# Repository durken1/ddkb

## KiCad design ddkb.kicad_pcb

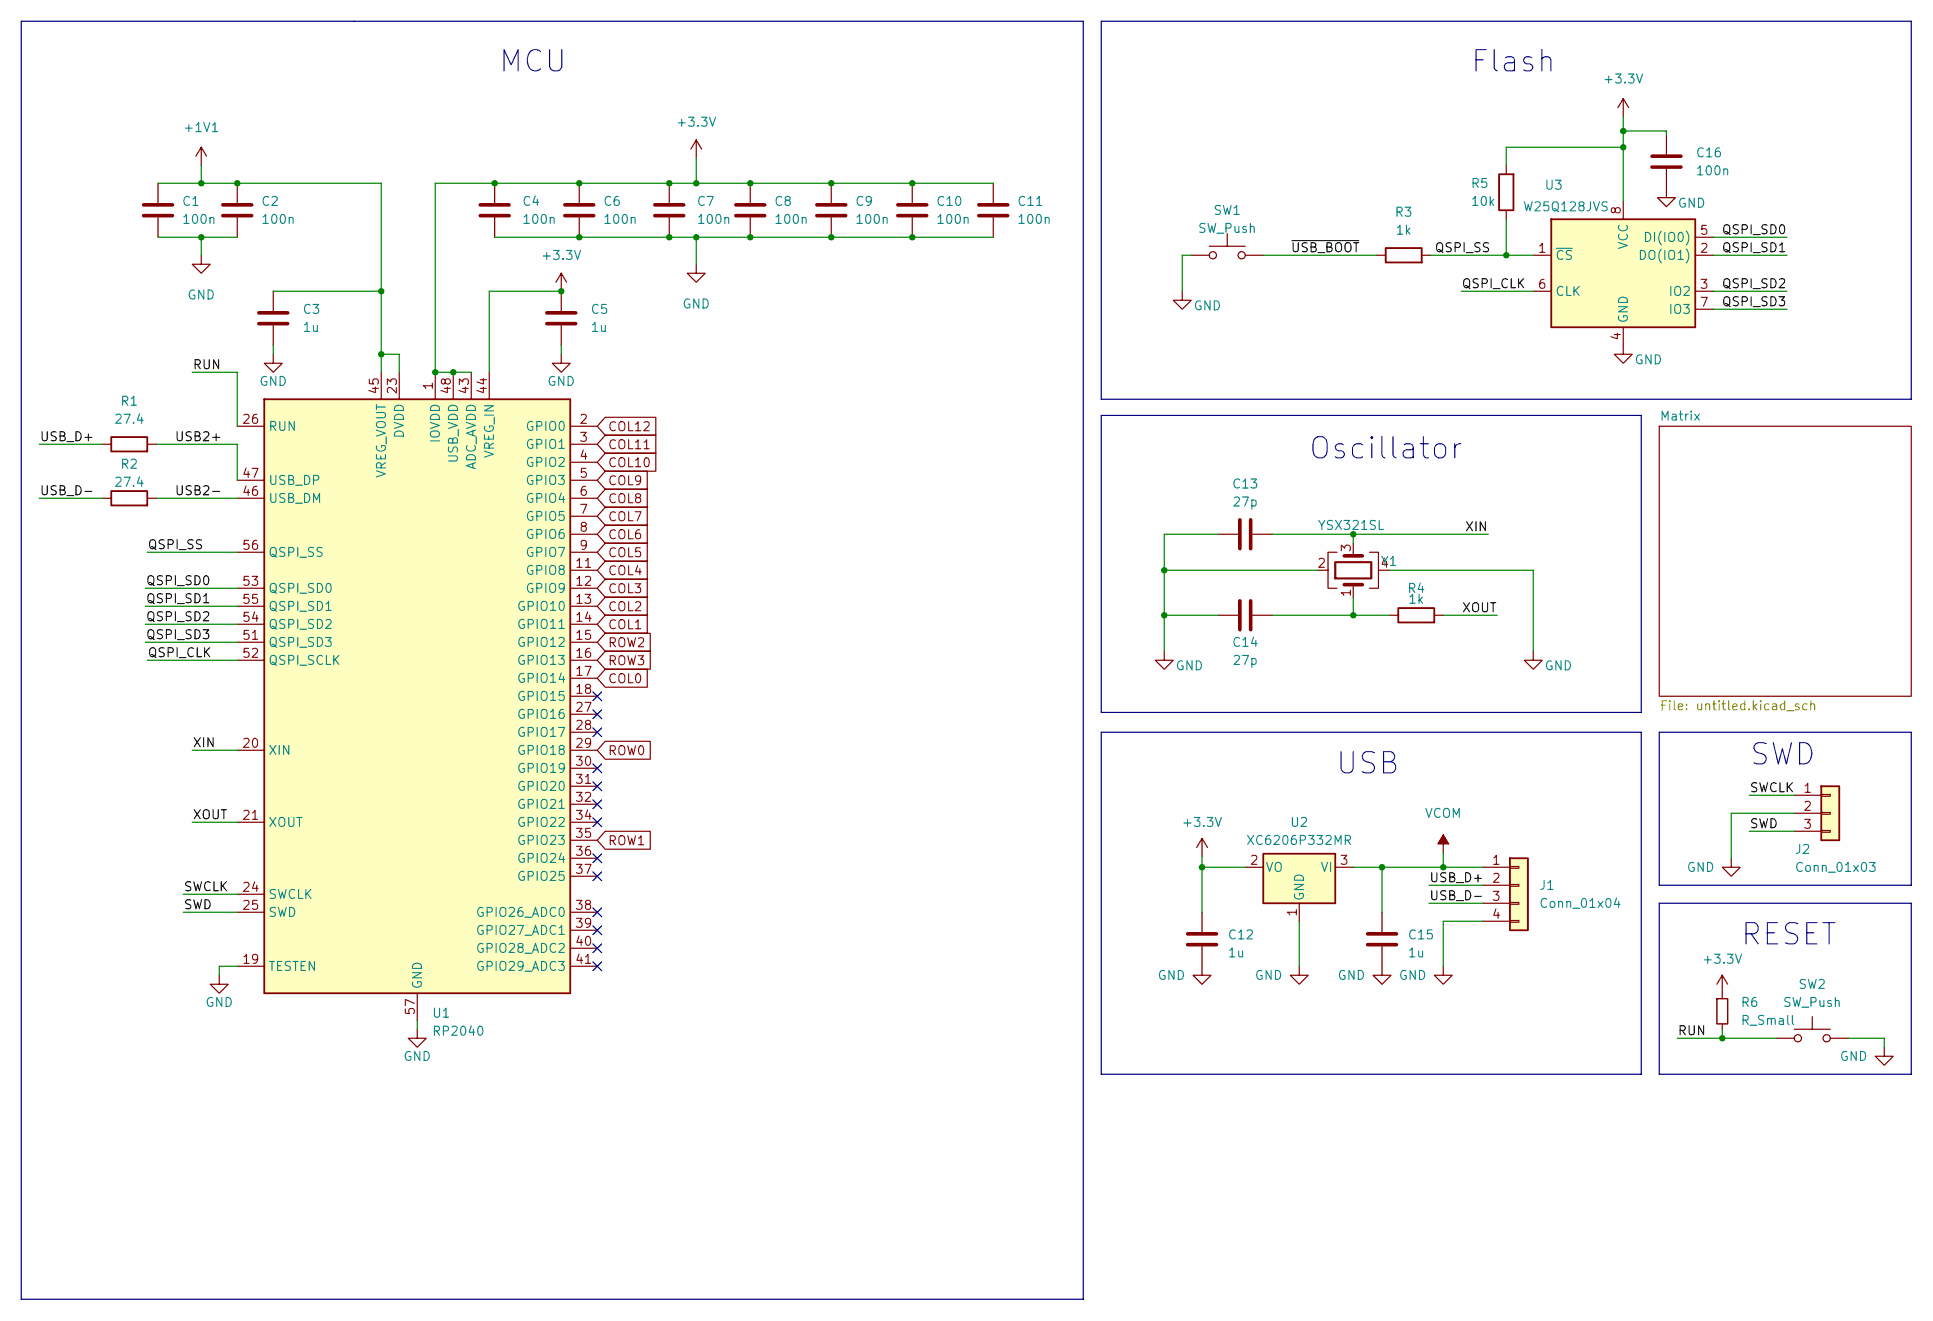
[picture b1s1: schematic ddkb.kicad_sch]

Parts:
C1, C2, C4, C6, C7, C8, C9, C10, C11, C16: 100n; C_0402_1005Metric
C3, C5, C12, C15: 1u; C_0402_1005Metric
C13, C14: 27p; C_0402_1005Metric
J1: Conn_01x04; JST_SH_SM04B-SRSS-TB_04x1.00mm_Angled
J2: Conn_01x03; PinHeader_1x03_P2.54mm_Vertical
R1, R2: 27.4; R_0402_1005Metric
R3, R4: 1k; R_0402_1005Metric
R5: 10k; R_0402_1005Metric
R6: R_Small; R_0402_1005Metric
SW1, SW2: SW_Push; SW_SPST_TL3342
U1: RP2040; QFN-56-1EP_7x7mm_P0.4mm_EP3.2x3.2mm
U2: XC6206P332MR; SOT-23-3
U3: W25Q128JVS; SOIC-8_5.23x5.23mm_P1.27mm
Y1: YSX321SL; Crystal_SMD_3225-4Pin_3.2x2.5mm

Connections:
+1V1: C1.1, C2.1, C3.1, U1.23 (DVDD), U1.45 (VREG_VOUT), U1.50 (DVDD)
+3.3V: C4.1, C5.1, C6.1, C7.1, C8.1, C9.1, C10.1, C11.1, C12.2, C16.1, R5.2, R6.1, U1.1 (IOVDD), U1.10 (IOVDD), U1.22 (IOVDD), U1.33 (IOVDD), U1.42 (IOVDD), U1.43 (ADC_AVDD), U1.44 (VREG_IN), U1.48 (USB_VDD), U1.49 (IOVDD), U2.2 (VO), U3.8 (VCC)
/QSPI_CLK: U1.52 (QSPI_SCLK), U3.6 (CLK)
/QSPI_SD0: U1.53 (QSPI_SD0), U3.5 (DI(IO0))
/QSPI_SD1: U1.55 (QSPI_SD1), U3.2 (DO(IO1))
/QSPI_SD2: U1.54 (QSPI_SD2), U3.3 (IO2)
/QSPI_SD3: U1.51 (QSPI_SD3), U3.7 (IO3)
/QSPI_SS: R3.2, R5.1, U1.56 (QSPI_SS), U3.1 (~CS)
/RUN: R6.2, SW2.1, U1.26 (RUN)
/SWCLK: J2.1, U1.24 (SWCLK)
/SWD: J2.3, U1.25 (SWD)
/USB2+: R1.2, U1.47 (USB_DP)
/USB2-: R2.2, U1.46 (USB_DM)
/USB_D+: J1.2, R1.1
/USB_D-: J1.3, R2.1
/XIN: C13.2, U1.20 (XIN), Y1.3
/XOUT: R4.2, U1.21 (XOUT)
/~USB_BOOT: R3.1, SW1.2
COL0: U1.17 (GPIO14); also elsewhere on the board
COL1: U1.14 (GPIO11); also elsewhere on the board
COL2: U1.13 (GPIO10); also elsewhere on the board
COL3: U1.12 (GPIO9); also elsewhere on the board
COL4: U1.11 (GPIO8); also elsewhere on the board
COL5: U1.9 (GPIO7); also elsewhere on the board
COL6: U1.8 (GPIO6); also elsewhere on the board
COL7: U1.7 (GPIO5); also elsewhere on the board
COL8: U1.6 (GPIO4); also elsewhere on the board
COL9: U1.5 (GPIO3); also elsewhere on the board
COL10: U1.4 (GPIO2); also elsewhere on the board
COL11: U1.3 (GPIO1); also elsewhere on the board
COL12: U1.2 (GPIO0); also elsewhere on the board
GND: C1.2, C2.2, C3.2, C4.2, C5.2, C6.2, C7.2, C8.2, C9.2, C10.2, C11.2, C12.1, C13.1, C14.1, C15.1, C16.2, J1.4, J2.2, SW1.1, SW2.2, U1.19 (TESTEN), U1.57 (GND), U2.1 (GND), U3.4 (GND), Y1.2, Y1.4
unnamed: C14.2, R4.1, Y1.1
ROW0: U1.29 (GPIO18); also elsewhere on the board
ROW1: U1.35 (GPIO23); also elsewhere on the board
ROW2: U1.15 (GPIO12); also elsewhere on the board
ROW3: U1.16 (GPIO13); also elsewhere on the board
VCOM: C15.2, J1.1, U2.3 (VI)

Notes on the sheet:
MCU
SWD
RESET
Oscillator
USB
Flash

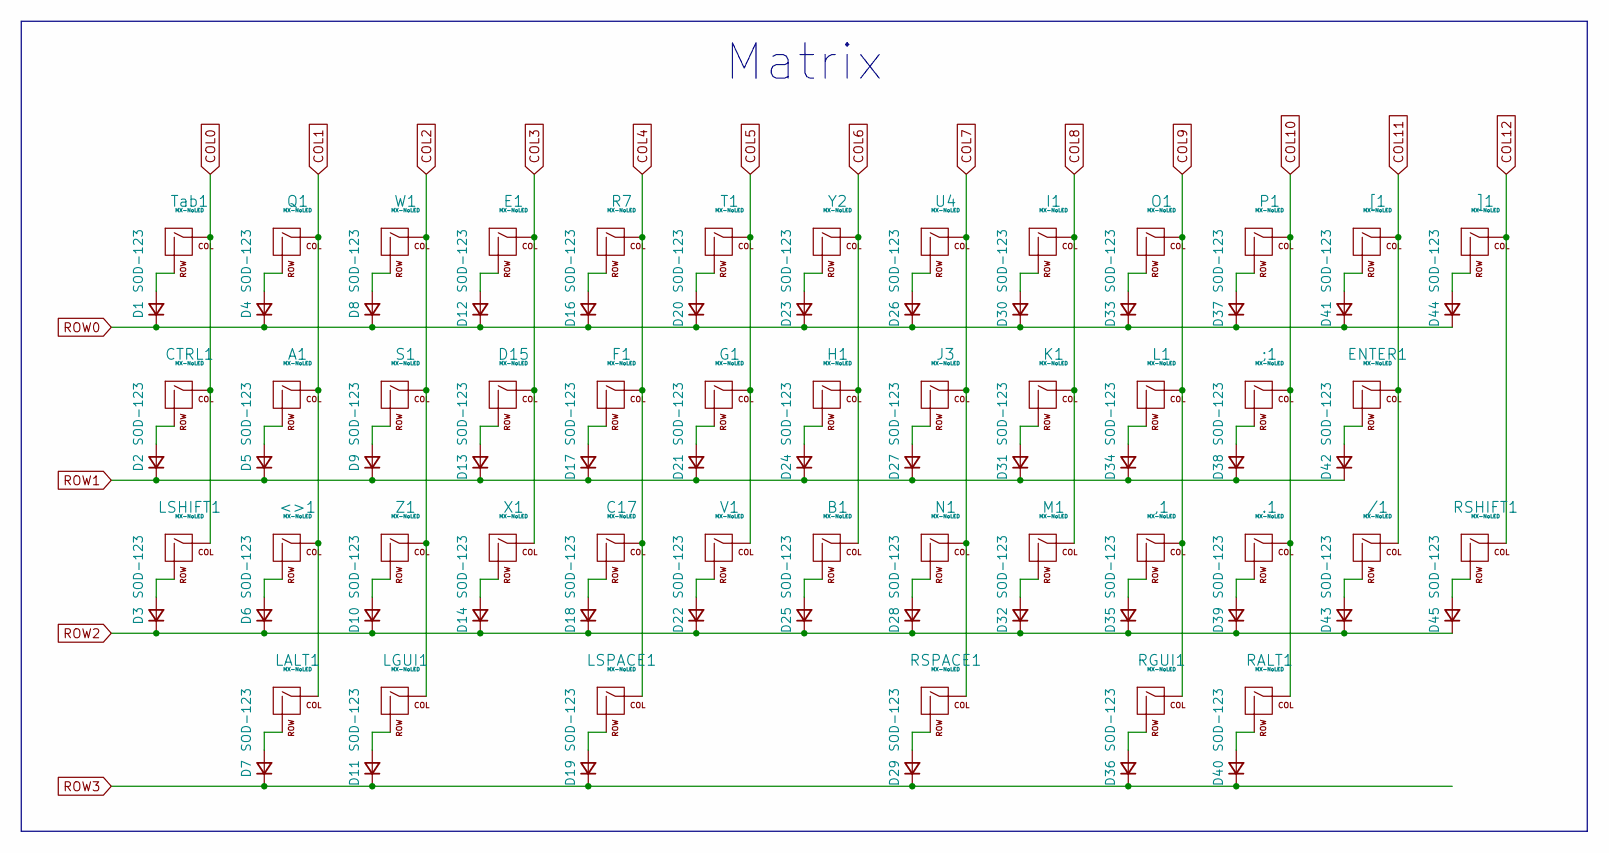
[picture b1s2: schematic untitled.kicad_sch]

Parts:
,1: MX-NoLED; MX-1U-NoLED
.1: MX-NoLED; MX-1U-NoLED
/1: MX-NoLED; MX-1U-NoLED
;1: MX-NoLED; MX-1U-NoLED
<>1: MX-NoLED; MX-1U-NoLED
A1: MX-NoLED; MX-1U-NoLED
B1: MX-NoLED; MX-1U-NoLED
C17: MX-NoLED; MX-1U-NoLED
CTRL1: MX-NoLED; MX-1.75U-NoLED
D1, D2, D3, D4, D5, D6, D7, D8, D9, D10, D11, D12, D13, D14, D16, D17, D18, D19, D20, D21, D22, D23, D24, D25, D26, D27, D28, D29, D30, D31, D32, D33, D34, D35, D36, D37, D38, D39, D40, D41, D42, D43, D44, D45: SOD-123; D_SOD-123
D15: MX-NoLED; MX-1U-NoLED
E1: MX-NoLED; MX-1U-NoLED
ENTER1: MX-NoLED; MX-1.75U-NoLED
F1: MX-NoLED; MX-1U-NoLED
G1: MX-NoLED; MX-1U-NoLED
H1: MX-NoLED; MX-1U-NoLED
I1: MX-NoLED; MX-1U-NoLED
J3: MX-NoLED; MX-1U-NoLED
K1: MX-NoLED; MX-1U-NoLED
L1: MX-NoLED; MX-1U-NoLED
LALT1: MX-NoLED; MX-1U-NoLED
LGUI1: MX-NoLED; MX-1U-NoLED
LSHIFT1: MX-NoLED; MX-2.25U-NoLED
LSPACE1: MX-NoLED; MX-3U-NoLED
M1: MX-NoLED; MX-1U-NoLED
N1: MX-NoLED; MX-1U-NoLED
O1: MX-NoLED; MX-1U-NoLED
P1: MX-NoLED; MX-1U-NoLED
Q1: MX-NoLED; MX-1U-NoLED
R7: MX-NoLED; MX-1U-NoLED
RALT1: MX-NoLED; MX-1U-NoLED
RGUI1: MX-NoLED; MX-1U-NoLED
RSHIFT1: MX-NoLED; MX-1.25U-NoLED
RSPACE1: MX-NoLED; MX-3U-NoLED
S1: MX-NoLED; MX-1U-NoLED
T1: MX-NoLED; MX-1U-NoLED
Tab1: MX-NoLED; MX-1.5U-NoLED
U4: MX-NoLED; MX-1U-NoLED
V1: MX-NoLED; MX-1U-NoLED
W1: MX-NoLED; MX-1U-NoLED
X1: MX-NoLED; MX-1U-NoLED
Y2: MX-NoLED; MX-1U-NoLED
Z1: MX-NoLED; MX-1U-NoLED
[1: MX-NoLED; MX-1U-NoLED
]1: MX-NoLED; MX-1U-NoLED

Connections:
COL0: CTRL1.1 (COL), LSHIFT1.1 (COL), Tab1.1 (COL); also elsewhere on the board
COL1: <>1.1 (COL), A1.1 (COL), LALT1.1 (COL), Q1.1 (COL); also elsewhere on the board
COL2: LGUI1.1 (COL), S1.1 (COL), W1.1 (COL), Z1.1 (COL); also elsewhere on the board
COL3: D15.1 (COL), E1.1 (COL), X1.1 (COL); also elsewhere on the board
COL4: C17.1 (COL), F1.1 (COL), LSPACE1.1 (COL), R7.1 (COL); also elsewhere on the board
COL5: G1.1 (COL), T1.1 (COL), V1.1 (COL); also elsewhere on the board
COL6: B1.1 (COL), H1.1 (COL), Y2.1 (COL); also elsewhere on the board
COL7: J3.1 (COL), N1.1 (COL), RSPACE1.1 (COL), U4.1 (COL); also elsewhere on the board
COL8: I1.1 (COL), K1.1 (COL), M1.1 (COL); also elsewhere on the board
COL9: ,1.1 (COL), L1.1 (COL), O1.1 (COL), RGUI1.1 (COL); also elsewhere on the board
COL10: .1.1 (COL), ;1.1 (COL), P1.1 (COL), RALT1.1 (COL); also elsewhere on the board
COL11: /1.1 (COL), ENTER1.1 (COL), [1.1 (COL); also elsewhere on the board
COL12: RSHIFT1.1 (COL), ]1.1 (COL); also elsewhere on the board
unnamed: ,1.2 (ROW), D35.2 (A)
unnamed: .1.2 (ROW), D39.2 (A)
unnamed: /1.2 (ROW), D43.2 (A)
unnamed: ;1.2 (ROW), D38.2 (A)
unnamed: <>1.2 (ROW), D6.2 (A)
unnamed: A1.2 (ROW), D5.2 (A)
unnamed: B1.2 (ROW), D25.2 (A)
unnamed: C17.2 (ROW), D18.2 (A)
unnamed: CTRL1.2 (ROW), D2.2 (A)
unnamed: D1.2 (A), Tab1.2 (ROW)
unnamed: D3.2 (A), LSHIFT1.2 (ROW)
unnamed: D4.2 (A), Q1.2 (ROW)
unnamed: D7.2 (A), LALT1.2 (ROW)
unnamed: D8.2 (A), W1.2 (ROW)
unnamed: D9.2 (A), S1.2 (ROW)
unnamed: D10.2 (A), Z1.2 (ROW)
unnamed: D11.2 (A), LGUI1.2 (ROW)
unnamed: D12.2 (A), E1.2 (ROW)
unnamed: D13.2 (A), D15.2 (ROW)
unnamed: D14.2 (A), X1.2 (ROW)
unnamed: D16.2 (A), R7.2 (ROW)
unnamed: D17.2 (A), F1.2 (ROW)
unnamed: D19.2 (A), LSPACE1.2 (ROW)
unnamed: D20.2 (A), T1.2 (ROW)
unnamed: D21.2 (A), G1.2 (ROW)
unnamed: D22.2 (A), V1.2 (ROW)
unnamed: D23.2 (A), Y2.2 (ROW)
unnamed: D24.2 (A), H1.2 (ROW)
unnamed: D26.2 (A), U4.2 (ROW)
unnamed: D27.2 (A), J3.2 (ROW)
unnamed: D28.2 (A), N1.2 (ROW)
unnamed: D29.2 (A), RSPACE1.2 (ROW)
unnamed: D30.2 (A), I1.2 (ROW)
unnamed: D31.2 (A), K1.2 (ROW)
unnamed: D32.2 (A), M1.2 (ROW)
unnamed: D33.2 (A), O1.2 (ROW)
unnamed: D34.2 (A), L1.2 (ROW)
unnamed: D36.2 (A), RGUI1.2 (ROW)
unnamed: D37.2 (A), P1.2 (ROW)
unnamed: D40.2 (A), RALT1.2 (ROW)
unnamed: D41.2 (A), [1.2 (ROW)
unnamed: D42.2 (A), ENTER1.2 (ROW)
unnamed: D44.2 (A), ]1.2 (ROW)
unnamed: D45.2 (A), RSHIFT1.2 (ROW)
ROW0: D1.1 (K), D4.1 (K), D8.1 (K), D12.1 (K), D16.1 (K), D20.1 (K), D23.1 (K), D26.1 (K), D30.1 (K), D33.1 (K), D37.1 (K), D41.1 (K), D44.1 (K); also elsewhere on the board
ROW1: D2.1 (K), D5.1 (K), D9.1 (K), D13.1 (K), D17.1 (K), D21.1 (K), D24.1 (K), D27.1 (K), D31.1 (K), D34.1 (K), D38.1 (K), D42.1 (K); also elsewhere on the board
ROW2: D3.1 (K), D6.1 (K), D10.1 (K), D14.1 (K), D18.1 (K), D22.1 (K), D25.1 (K), D28.1 (K), D32.1 (K), D35.1 (K), D39.1 (K), D43.1 (K), D45.1 (K); also elsewhere on the board
ROW3: D7.1 (K), D11.1 (K), D19.1 (K), D29.1 (K), D36.1 (K), D40.1 (K); also elsewhere on the board

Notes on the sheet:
Matrix

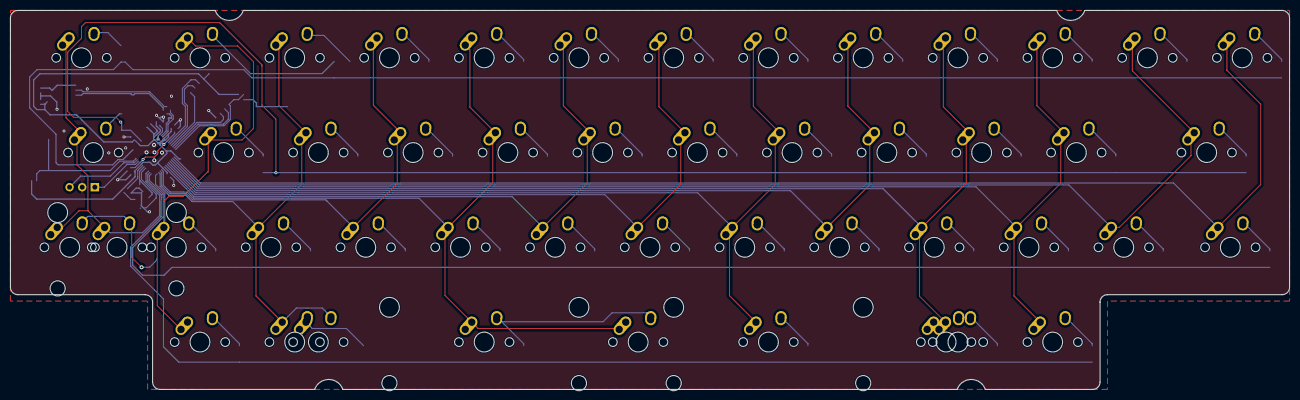
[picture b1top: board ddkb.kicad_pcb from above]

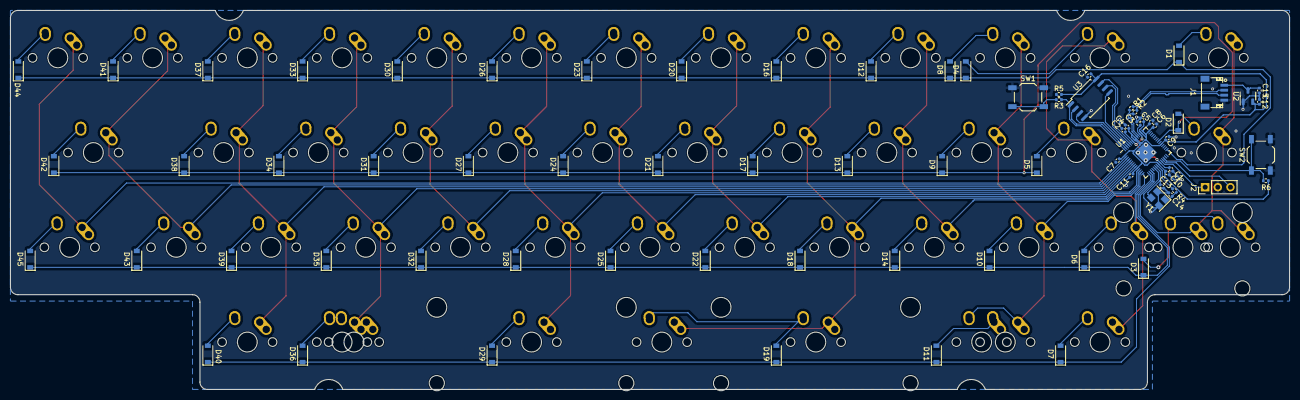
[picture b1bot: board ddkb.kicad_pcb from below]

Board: 2 copper layers, 257.2 x 76.2 mm, 118 parts (74 on the bottom side), 82 nets.

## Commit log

2023-03-27 add pcb
2023-03-27 small reroutes
2023-03-27 indrease jst marigin
2023-03-27 add second bottom row
2023-03-27 small adjustment
2023-03-28 add split left shift
2023-03-28 change ldo
2023-03-28 add qspi_ss pullup
2023-04-04 cleanup
